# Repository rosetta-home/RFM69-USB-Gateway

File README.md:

# RFM69-USB-Gateway
This is a USB gateway for the RFM69 FSK module. Incoming wireless data is sent to the host computer over serial.

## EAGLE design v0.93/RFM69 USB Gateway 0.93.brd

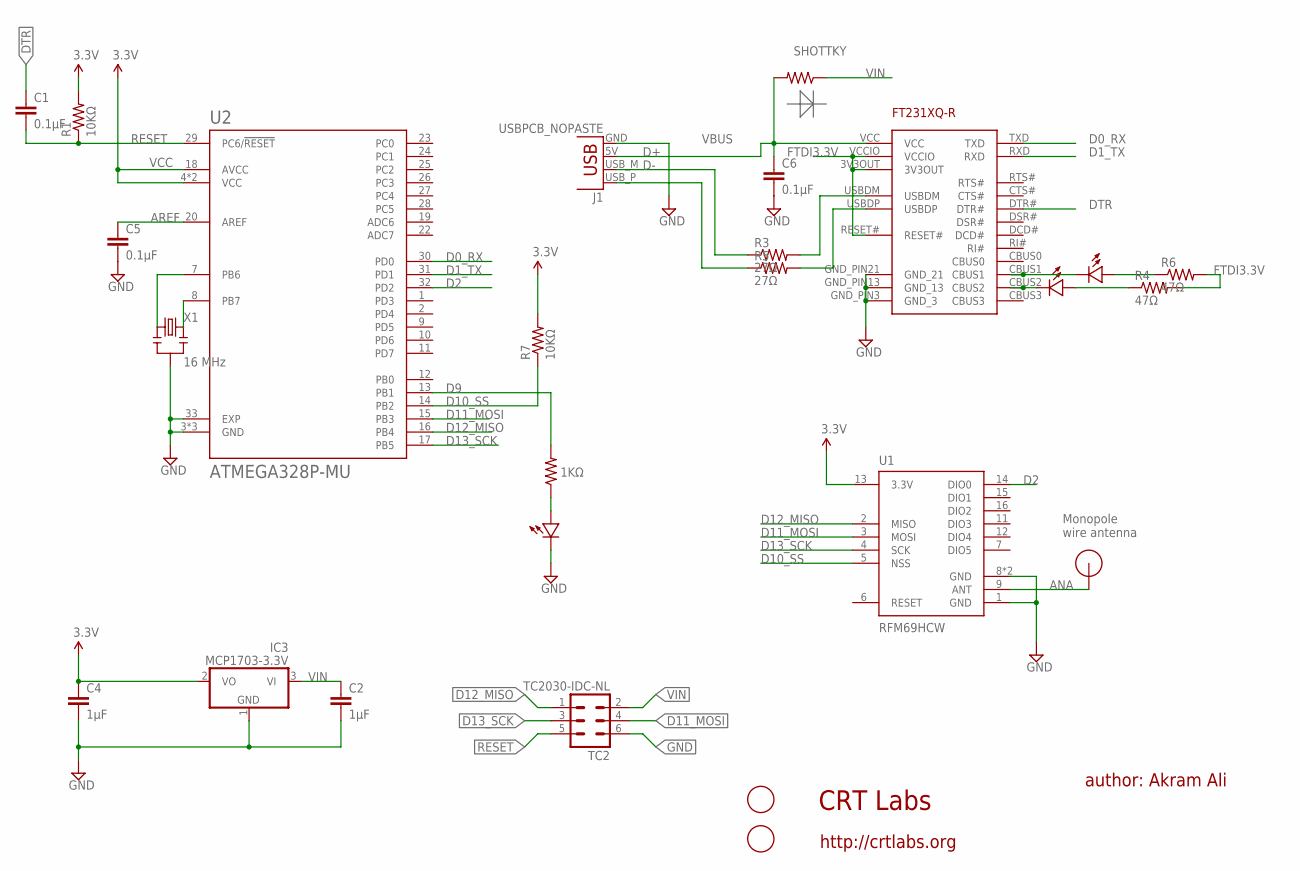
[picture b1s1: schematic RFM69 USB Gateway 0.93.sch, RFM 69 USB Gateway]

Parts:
C1, C5, C6: 0.1μF; 0805; MPN CC0805KRX7R9BB104
C2, C4: 1μF; 0805; MPN CC0805ZRY5V8BB105
D: SHOTTKY; 0805; MPN SD0805S040S0R5
FT231XQ-R: FT231XQ-R; FTDI_FT231XQ-R_PACKAGE; MPN FT231XQ-R
IC3: MCP1703-3.3V; SOT23; MPN MCP1703T-2502E/CB
J1: USBPCB_NOPASTE; USB-A-PCB-NOPASTE
R1, R7: 10KΩ; 0805; MPN RC0805FR-0710KL
R2: 1KΩ; 0805; MPN RC0805FR-071KL
R3, R5: 27Ω; 0805; MPN RC0805FR-0727RL
R4, R6: 47Ω; 0805; MPN RC0805FR-0747RL
RX: Green; 0805-LED; MPN LG R971-KN-1
TC2: TC2030-IDC-NL
TX: Red; 0805-LED; MPN LG R971-KN-1
U1: RFM69HCW; RFM69HCW-XXXS2; MPN RFM69HW
U2: ATMEGA328P-MU; QFN50P500X500X100-33N; MPN ATmega328P-MU
U$2: Status; 0805-LED; MPN LG R971-KN-1
U$3, U$4: FIDUCIAL; FIDUCIAL_1MM
U$6: RFM12B_ANTENNA; RFM12B-ANTENNA
X1: 16 MHz; RESONATOR-SMD; MPN CSTCE16M0V53-R0

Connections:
ANA: U1.9 (ANT), U$6.P$1
AREF: C5.1, U2.20 (AREF)
D0_RX: FT231XQ-R.TXD, U2.30 (PD0)
D1_TX: FT231XQ-R.RXD, U2.31 (PD1)
D2: U1.14 (DIO0), U2.32 (PD2)
D9: R2.2, U2.13 (PB1)
D10_SS: R7.1, U1.5 (NSS), U2.14 (PB2)
D11_MOSI: TC2.4, U1.3 (MOSI), U2.15 (PB3)
D12_MISO: TC2.1, U1.2 (MISO), U2.16 (PB4)
D13_SCK: TC2.3, U1.4 (SCK), U2.17 (PB5)
D+: J1.USB_P (D+), R5.1
D-: J1.USB_M (D-), R3.1
DTR: C1.1, FT231XQ-R.DTR#
FTDI3.3V: FT231XQ-R.3V3OUT, FT231XQ-R.RESET#, FT231XQ-R.VCCIO, R4.2, R6.2
GND: C2.2, C4.2, C5.2, C6.2, FT231XQ-R.GND_PIN3 (GND_3), FT231XQ-R.GND_PIN13 (GND_13), FT231XQ-R.GND_PIN21 (GND_21), IC3.1 (GND), J1.GND, TC2.6, U1.1 (GND), U1.8 (GND), U1.10 (GND), U2.3 (GND), U2.5 (GND), U2.21 (GND), U2.33 (EXP), U$2.MINUS, X1.2
unnamed: U2.7 (PB6), X1.1
unnamed: R2.1, U$2.PLUS
unnamed: FT231XQ-R.USBDM, R3.2
unnamed: FT231XQ-R.USBDP, R5.2
unnamed: FT231XQ-R.CBUS1, RX.MINUS
unnamed: FT231XQ-R.CBUS2, TX.MINUS
unnamed: R4.1, TX.PLUS
unnamed: R6.1, RX.PLUS
unnamed: U2.8 (PB7), X1.3
RESET: C1.2, R1.1, TC2.5, U2.29 (PC6/!RESET)
VBUS: C6.1, D.2, FT231XQ-R.VCC, J1.5V (VBUS)
VCC: C4.1, IC3.2 (VO), R1.2, R7.2, U1.13 (3.3V), U2.4 (VCC), U2.6 (VCC), U2.18 (AVCC)
VIN: C2.1, D.1, IC3.3 (VI), TC2.2

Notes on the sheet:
CRT Labs
author: Akram Ali
http://crtlabs.org
Monopole wire antenna

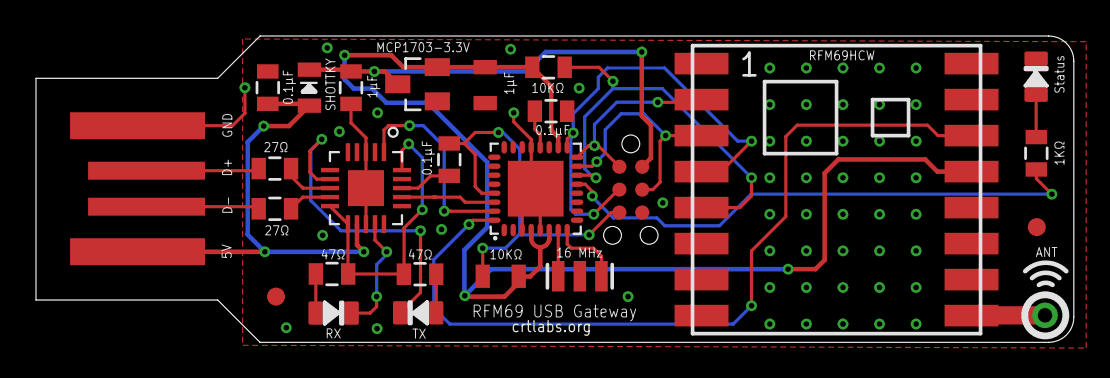
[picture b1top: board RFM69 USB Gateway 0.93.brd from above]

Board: 2 copper layers, 57.7 x 17.0 mm, 26 parts (0 on the bottom side), 28 nets.

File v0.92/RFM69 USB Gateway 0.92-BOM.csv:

Qty,Value,Device,Package,Parts,Description,MPN
3,.1uf,CAP0805,805,C1-C5-C6,Capacitor,CC0805KRX7R9BB104
2,10k,RESISTOR0805,805,R1,Resistor,RC0805FR-0710KL
1,16 MHz,RESONATORSMD,RESONATOR-SMD,X1,Resonator,CSTCE16M0V53-R0
1,1k,RESISTOR0805-RES,805,R2,Resistor,RC0805FR-071KL
2,1uf,CAP0805,805,C2-C4,Capacitor,CC0805ZRY5V8BB105
2,27,RESISTOR0805-RES,805,R3-R5,Resistor,RC0805FR-0727RL
2,47,RESISTOR0805-RES,805,R4-R6,Resistor,RC0805FR-0747RL 
1,ATmega328P-MU,ATmega328P-MU,QFN50P500X500X100-33N,U2,ATmega328P-MU,ATmega328P-MU
1,FT231XQ-R,FT231XQ-R,FTDI_FT231XQ-R_PACKAGE,FT231XQ-R,This is the 20-LD QFN package of the FTDI FT231XQ-R chip.,FT231XQ-R
2,LED,LED0805,0805-LED,RX-TX,,LG R971-KN-1
1,MCP1703-3.3V,MCP1703CB,SOT23,IC3,250 mA-16V-Low Quiescent Current LDO Regulator,MCP1703T-2502E/CB
1,RFM69HCW,RFM69HCW,RFM69HCW-XXXS2,U1,,RFM69HW
1,SHOTTKY,RESISTOR0805,805,D,Resistor,SD0805S040S0R5
1,Status,LED0805,0805-LED,U$2,,LG R971-KN-1

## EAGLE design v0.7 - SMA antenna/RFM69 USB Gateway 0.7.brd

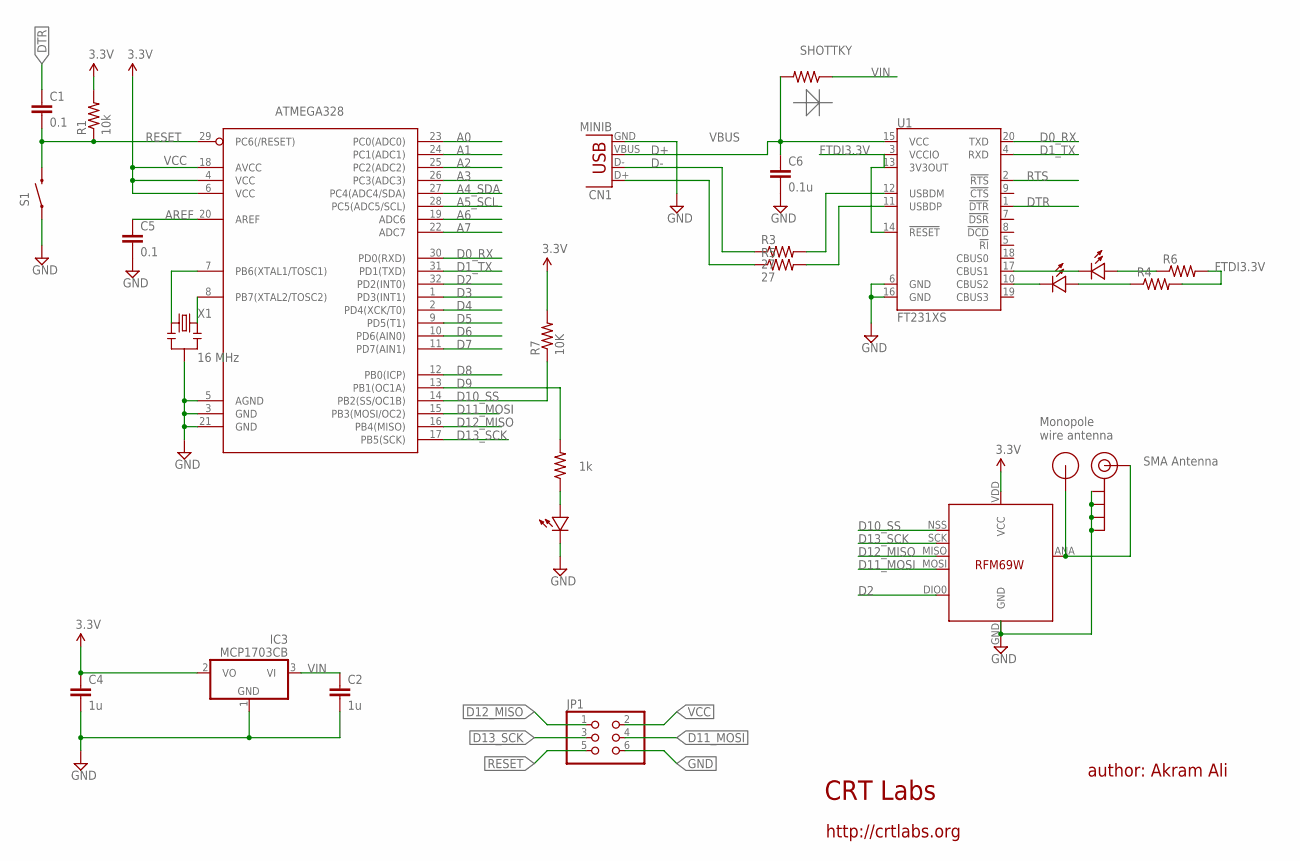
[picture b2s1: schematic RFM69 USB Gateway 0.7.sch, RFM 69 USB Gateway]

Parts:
ATMEGA328: ATMega-328; TQFP32-08
C1, C5: 0.1; 0805
C2, C4: 1u; 0805
C6: 0.1u; 0805
CN1: MINIB; USB-A-H
D: SHOTTKY; 0805
IC3: MCP1703CB; SOT23
J$1: SMA_EDGE; SMA-EDGE
JP1: PINHD-2X3; 2X03
R1: 10k; 0805
R2: 1k; 0805
R3, R5: 27; 0805
R4, R6: RESISTOR0805-RES; 0805
R7: 10K; 0805
S1: SWITCH-MOMENTARY-2SMD-ALT01; TACTILE-SWITCH-SMD-ALT01
U1: FT231XS; SSOP20_L
U$1: RFM12B_ANTENNA; RFM12B-ANTENNA
U$2, U$4, U$7: LED0805; 0805-LED
U$5: RFM69; RFM69W-MINPADS
X1: 16 MHz; RESONATOR-SMD

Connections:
A0: ATMEGA328.23 (PC0(ADC0))
A1: ATMEGA328.24 (PC1(ADC1))
A2: ATMEGA328.25 (PC2(ADC2))
A3: ATMEGA328.26 (PC3(ADC3))
A4_SDA: ATMEGA328.27 (PC4(ADC4/SDA))
A5_SCL: ATMEGA328.28 (PC5(ADC5/SCL))
A6: ATMEGA328.19 (ADC6)
A7: ATMEGA328.22 (ADC7)
AREF: ATMEGA328.20 (AREF), C5.1
D0_RX: ATMEGA328.30 (PD0(RXD)), U1.20 (TXD)
D1_TX: ATMEGA328.31 (PD1(TXD)), U1.4 (RXD)
D2: ATMEGA328.32 (PD2(INT0)), U$5.DIO0
D3: ATMEGA328.1 (PD3(INT1))
D4: ATMEGA328.2 (PD4(XCK/T0))
D5: ATMEGA328.9 (PD5(T1))
D6: ATMEGA328.10 (PD6(AIN0))
D7: ATMEGA328.11 (PD7(AIN1))
D8: ATMEGA328.12 (PB0(ICP))
D9: ATMEGA328.13 (PB1(OC1A)), R2.2
D10_SS: ATMEGA328.14 (PB2(SS/OC1B)), R7.1, U$5.NSS (SEL)
D11_MOSI: ATMEGA328.15 (PB3(MOSI/OC2)), JP1.4, U$5.MOSI
D12_MISO: ATMEGA328.16 (PB4(MISO)), JP1.1, U$5.MISO
D13_SCK: ATMEGA328.17 (PB5(SCK)), JP1.3, U$5.SCK
D+: CN1.D+, R5.1
D-: CN1.D-, R3.1
DTR: C1.1, U1.1 (!DTR)
FTDI3.3V: R4.2, R6.2, U1.3 (VCCIO), U1.13 (3V3OUT), U1.14 (!RESET)
GND: ATMEGA328.3 (GND), ATMEGA328.5 (AGND), ATMEGA328.21 (GND), C2.2, C4.2, C5.2, C6.2, CN1.GND, IC3.1 (GND), J$1.GND@0 (GND), J$1.GND@1 (GND), J$1.GND@2 (GND), J$1.GND@3 (GND), JP1.6, S1.1, S1.2 (1), U1.6 (GND), U1.16 (GND), U$2.MINUS, U$5.GND, X1.2
unnamed: ATMEGA328.7 (PB6(XTAL1/TOSC1)), X1.1
unnamed: R2.1, U$2.PLUS
unnamed: J$1.SIG (SIGNAL), U$1.P$1, U$5.ANA (ANT)
unnamed: R3.2, U1.12 (USBDM)
unnamed: R5.2, U1.11 (USBDP)
unnamed: U1.17 (CBUS1), U$4.MINUS
unnamed: U1.10 (CBUS2), U$7.MINUS
unnamed: R4.1, U$7.PLUS
unnamed: R6.1, U$4.PLUS
unnamed: ATMEGA328.8 (PB7(XTAL2/TOSC2)), X1.3
RESET: ATMEGA328.29 (PC6(/RESET)), C1.2, JP1.5, R1.1, S1.3 (2), S1.4 (2)
RTS: U1.2 (!RTS)
VBUS: C6.1, CN1.VBUS, D.2, U1.15 (VCC)
VCC: ATMEGA328.4 (VCC), ATMEGA328.6 (VCC), ATMEGA328.18 (AVCC), C4.1, IC3.2 (VO), JP1.2, R1.2, R7.2, U$5.VDD (VCC)
VIN: C2.1, D.1, IC3.3 (VI)

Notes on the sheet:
CRT Labs
author: Akram Ali
http://crtlabs.org
SMA Antenna
Monopole wire antenna

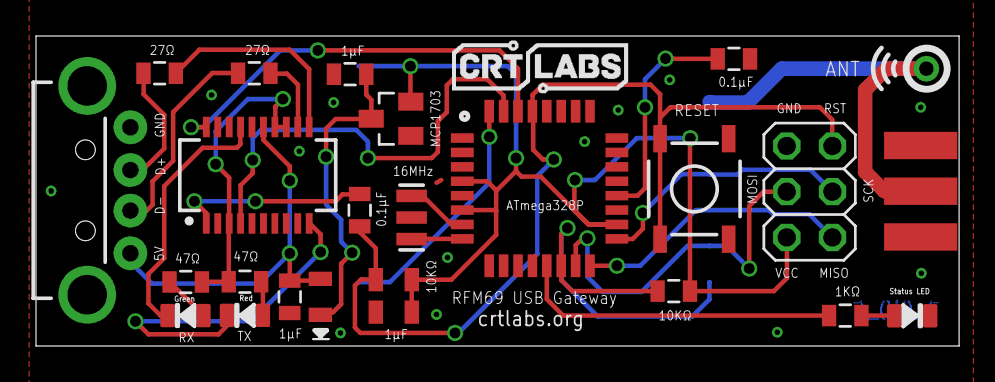
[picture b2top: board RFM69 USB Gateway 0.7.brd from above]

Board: 2 copper layers, 51.3 x 17.2 mm, 26 parts (1 on the bottom side), 28 nets.

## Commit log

2016-07-01 Eagle files for USB gateway
    v0.2
2016-07-15 USB jack adjustments
    v0.3 - Adjusted edge of board a little to accommodate groove of USB jack
2016-07-15 Remove unnecessary files
2016-07-20 Added pic
2016-07-21 Added ISP header and reset button
    v0.4
    - ISP header
    - Reset button
    - Silk screen for all components
    - Slight rearrangement
2016-07-21 Fixed overlapping traces
2016-07-21 OSH Park PCB layout
2016-08-03 Added pullup on CS line
    10K pullup on CS for allowing ISP programming
    Changed all components to 0805 size
2016-08-03 Silkscreen minor edits
2016-08-03 Added pullup on CS (pin 10)
    10K pullup on CS (RFM69) to avoid issues during ISP programming
    Changed all components to 0805 size
2016-08-03 v0.5 OSHpark render
2016-08-03 PCB render from oshpark.com
2016-09-08 PDF schematic added
2016-09-22 v0.6 - fixed auto reset, adjusted traces
    Added 0.1 uF cap on reset, series with DTR (allows auto reset via FTDI)
    Moved some components to accommodate the cap
    Adjusted several traces
    Made GND vias more consistent in size
2016-09-22 Updated the PDF schematic
    v0.6
2016-09-22 Adjusted D- trace
2016-09-22 Minor silkscreen adjustments
2016-09-22 Ignore lck files
2016-09-22 Added CRT Labs logo
2016-09-22 Updated OSH Park render to v0.6
2016-09-22 Updated OSH Park render
2016-09-22 Added back PCB render
2016-09-22 v0.7 - added SMA connector
    Moved some components around to accommodate for SMA connector and clean
    up some traces
2016-09-22 Touch up schematic
2016-09-22 Deleted old schematic
2016-09-22 Deleted scr file
2016-09-22 Added v0.7 renders
    v0.7 has SMA antenna, some components moved a bit to accommodate for
    it. Board length is slightly longer than v0.6, but everything else is
    the same.
2016-09-22 Rounded corners of board
2016-09-22 Updated OSH Park render
    v0.7 with rounded corners
2016-10-18 v0.8 - Changed packages to QFN - **WIP**
    ! Traces not connected !
2016-10-18 Silkscreen
2016-10-25 Routed all traces
    Rearranged components on the board
2016-10-25 Deleted shrug emoji because no space :( but oh well ¯\_(ツ)_/¯
2016-10-25 Unsmashed and updated all component values
2016-10-25 Fixed silkscreen
    Changed all fonts to vector; silkscreen now on layer 121, adjusted some
    components and traces
2016-10-25 Adjusted silkscreen
2016-10-25 Added REALTOR R to silkscreen
2016-10-25 Added OSHPark renders
2016-10-25 Organized folders
2016-10-25 Added PDF schematic for v0.8
2016-10-25 Minor trace adjustments
2016-10-25 Updated OSH Park renders
2016-11-14 Added firmware for USB gateway
2017-02-06 v0.9 - Integrated USB jack into PCB
    - removed USB A jack and integrated into PCB. 2.4mm thickness required
    for a tight fit into USB port.
    - made VCC traces slightly thicker.
2017-02-07 v0.91 moving RFM69 to top side
    traces still incomplete
2017-02-07 Made ground pours on bottom more even
    Added extra stitching vias; changed very thin line-like pours to thicker
    and fatter (ish) ones; minor touchups
2017-02-13 Connected all traces
2017-03-16 Minor firmware update
    LED will only blink after ACK is requested and sent
2017-03-22 v0.92 - design update
    - Removed ISP headers (flash using MLF/QFN socket - for advanced users
    only) use v0.8 or v0.9 for ISP headers
    - Removed SMA pads (just use wire monopole 82mm for 915MHz)
    - Replaced RFM69HW with RFM69HCW
    - Reduced overall size of board
    - Rerouted several traces to fit new design
2017-03-22 Relocated a via
    for better silkscreen
2017-03-29 adding bom for v.92
2017-03-29 adding mpns to schematic
2017-03-30 updated mpn to ATmega328P-MU
2017-03-30 added eagle temp files to git ignore
2017-03-30 synchronized brd file
2017-04-03 Fixed mirrored logo
    lol how did that happen
2017-05-24 use serial flush and do not require ack to push data over serial
2017-11-18 v0.93 update
    - Added tag connect ISP header for programming
    - board dimensions slightly increased to accomodate tag connect
    - Adjusted several traces to accomodate new header
    - Increased all via drill sizes to 12 mil (0.3mm)
    - Reduced thickness of USB part from 12.54mm to 12.30mm
    - minor silk screen adjustments
2017-12-05 Added gerbers and BOM
2017-12-19 initial sending of configuration commands
2017-12-20 update send function
2017-12-20 remove Serial debugging
2018-01-19 BOM update
2018-02-28 Create LICENSE
2018-04-18 ack sooner
2018-04-18 just kidding

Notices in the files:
parts and their libraries:
SparkFun-DigitalIC: Licensing: CC v3.0 Share-Alike You are welcome to use this library for commercial purposes.
SparkFun-Connectors: Licensing: Creative Commons ShareAlike 4.0 International - https://creativecommons.org/licenses/by-sa/4.0
